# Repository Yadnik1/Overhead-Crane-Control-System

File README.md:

# Overhead-Crane-Control-System
An efficient and reliable embedded system firmware for overhead crane applications. Developed using STM32G030C8T6 MCU, this project presents a specialized solution for encoder and decoder units, tailored to enhance the performance and safety of crane operations. The project firmware comprises three fundamental components: the encoder unit (remote control), the decoder unit (crane control system), and the EEPROM configuration software.

## Decoder Unit

This code serves as the core control unit for an overhead crane system, managing bidirectional communication between master and slave devices using the NRF905 module. It detects the device's operational mode based on the state of the `MODE_Pin` and initializes the NRF905 module, shift registers, and relays during startup. The NRF905 module constantly listens for incoming data, with a rising edge on the `DR_Pin` indicating data reception. Upon receiving specific patterns like `0x40000000`, it activates the NRF905 module and the system eventually, while `0x80000000` sets the receiver state to standby and turns off the system. Relay states are updated through shift registers to control crane operations.

Additionally, the code utilizes timer interrupts to enhance control. The `HAL_TIM_Base_Start_IT(&htim3)` function initiates timer 3 and enables its interrupts, allowing for precise timing operations. Timer interrupts can be used for various purposes within the code, such as coordinating time-sensitive tasks or ensuring precise timing for specific crane operations.

The code not only manages data reception and relay control but also implements crucial button toggle and interlock features. Button presses, particularly those involving button 3, are monitored and toggled through the `button3_state` variable. Interlock functionality is achieved by clearing relay bits associated with buttons 5 and 6 if both buttons are pressed simultaneously. These 2 functionalities are often used in overhead cranes for numerous applications apart from normal relay actuation.

The decoder firmware can be found in the Firmware folder in Decoder.c file.

### Standalone Decoder Unit

## Encoder Unit

The encoder unit interfaces with a set of buttons representing different crane functions, such as movement and relay control. The system relies on the NRF905 wireless module for communication between the encoder unit and the crane's decoder unit. The encoder unit continuously monitors the state of these buttons and generates a 32-bit pattern based on the button configuration. This pattern is then transmitted using the NRF905 module to the decoder unit, allowing it to interpret and execute the corresponding crane operations.

The encoder unit also incorporates timer interrupts, which are crucial for efficient button polling and data transmission. Timer interrupts ensure that button states are checked periodically, preventing excessive data transmission while maintaining responsiveness to button presses. Additionally, the code includes logic for switching on and off specific crane functions based on the received data, enabling the operator to control various aspects of the crane's operation remotely. Overall, the encoder unit plays a vital role in facilitating remote crane control, ensuring safety and precision in crane operations, and enhancing the efficiency of overhead crane systems.

The encoder firmware can be found in the Firmware folder in Encoder.c file.

### Standalone Encoder Unit

### Encoder-Decoder Unit Set

### Powered Encoder-Decoder Unit Set

Additionally, I also worked towards the development of the two-sided encoder unit PCB as seen below: 

### PCB of the Encoder Unit

## EEPROM Configuration

The provided code serves as a critical component for configuring the decoder unit, facilitating the mapping of each key on the encoder to its respective relay on the decoder. This functionality is essential in scenarios where customization and flexibility are paramount, such as when an original equipment manufacturer (OEM) needs to provide a system that can adapt to the unique button-to-relay configurations of multiple clients. The code enables the OEM to initialize and manage memory structures that store the configuration data for different keys and sectors within the decoder. It supports both default settings and runtime customization of these configurations through AT commands received via UART.

The code's working involves several key aspects. First, it initializes the memory with default values for each key and sector, ensuring a consistent starting point. Second, it processes AT commands sent over UART to customize the configuration, allowing the OEM or clients to modify the relay assignments for specific keys dynamically. Third, it employs Flash memory to store these configurations persistently, ensuring that the settings are retained even after power cycles. Lastly, it provides feedback to the user or clients through debug messages sent over UART, facilitating troubleshooting and verification of the configurations. This code serves as a robust and adaptable solution for managing button-to-relay mappings in a versatile and client-specific manner, making it highly valuable for the OEM's system customization needs.

The EEPROM configuration firmware can be found in the Firmware folder in EEPROM.c file.

### Testing and Configuring the Decoder Unit

## Final Application:

The final appliation can be as seen from the image below, where the power circuitry and the enclosure is applied on the encoder and decoder units before sending it to the end client.

### Application Ready Overhead-Crane-Control-System

Complete working of the system before can be seen in this video: https://bit.ly/48JevyT

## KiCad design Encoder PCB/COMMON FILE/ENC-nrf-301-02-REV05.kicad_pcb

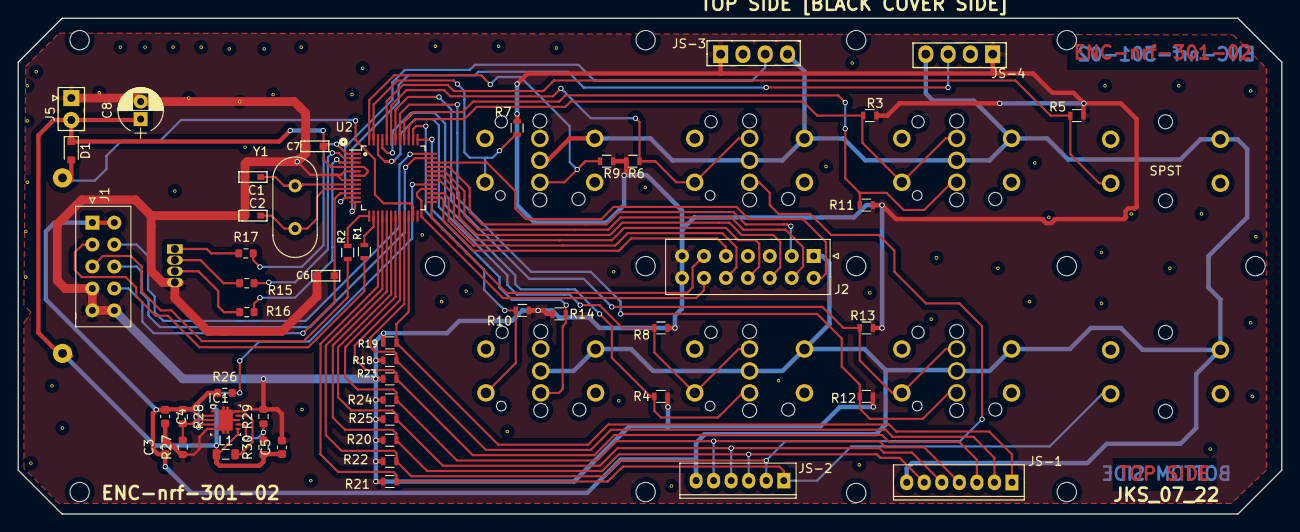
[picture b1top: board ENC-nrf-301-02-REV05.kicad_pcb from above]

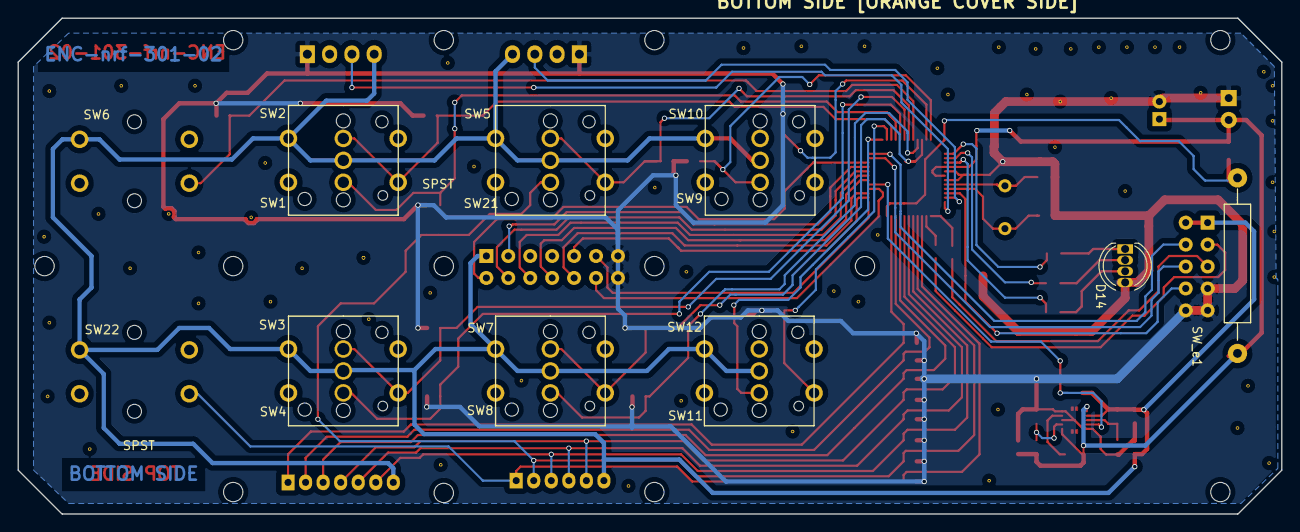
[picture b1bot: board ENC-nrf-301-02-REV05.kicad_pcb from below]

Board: 2 copper layers, 144.0 x 56.5 mm, 66 parts (8 on the bottom side), 54 nets.

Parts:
C1, C2: C; MS_0603
C3: CP1; C_0603_1608Metric
C4, C5: C; C_0603_1608Metric
C6, C7: C; HS_0603
C8: C; CP_Radial_D5.0mm_P2.00mm
D1: D; D_0805
D14: LED_3528; LED_D5.0mm-4
IC1: TPS61020DRCR
J1: CONN_5X2; CON_2X5_2.54MM
J2: CONN_7X2; CONN_2X7_2.54MM
J5: CONN_2; 2.5MM_BERGE
JS-1: CONN_7; CON_2.0MM_7PIN
JS-2: CONN_6; CON_2.0MM_6PIN
JS-3, JS-4: CONN_4; 2.54MM_BERGE_4PIN
L1: L; L_0805_2012Metric
R1, R2, R3, R4, R5, R6, R7, R8, R9, R10, R11, R12, R13, R14, R18, R19, R20, R21, R22, R23, R24, R25: R; R_0603
R15, R16, R17, R26, R27, R28, R29, R30: R; R_0603_1608Metric
SW1, SW4, SW6, SW8, SW9, SW12, SW21, SW22: SPST; SW_ALPS_TACT
SW2, SW3, SW5, SW7, SW10, SW11: SPST; SW_MARKQUARD
SW_e1: RD_RELAY; RELAY_REED_L20W2.5
U2: STM32G030C6T6; LQFP-48_7x7mm_Pitch0.5mm
Y1: Crystal; Crystal_HC49-4H_Vertical

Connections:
+3.3V: C3.1, C4.1, IC1.2, J1.1, J1.2, J2.1, JS-1.7, JS-2.6, JS-3.4, JS-4.4, R26.1, R28.1, SW1.2, SW2.3, SW3.3, SW4.2, SW5.3, SW6.2, SW7.3, SW8.2, SW9.2, SW10.3, SW11.3, SW12.2, SW21.1, SW22.1
/AI1: JS-3.3, U2.11
/AI2: JS-4.3, U2.12
/CD: J2.6, U2.31
/CSN: J2.12, U2.28
/DBG_RX: R1.2, U2.14
/DGB_TX: R2.2, U2.13
/DR: J2.8, U2.30
/MISO: J2.9, U2.26
/MOSI: J2.10, U2.27
/NRST: C6.1, J1.8, U2.10
/PW_UP: J2.4, U2.32
/REED_PIN: D1.2, SW_e1.2, U2.23
/SCK: J2.11, U2.25
/SWCLK: J1.4, U2.36
/SWDIO: J1.6, U2.35
/TRX_CE: J2.3, U2.33
/TX_EN: J2.2, U2.34
/VBAT: C5.1, C7.1, C8.1, D1.1, IC1.1, IC1.6, J5.2, L1.1, R30.1, SW_e1.1, U2.4, U2.6
GND: C1.2, C2.2, C3.2, C4.2, C5.2, C6.2, C7.2, C8.2, D14.4, IC1.5, IC1.8, IC1.10, IC1.11, J1.7, J1.9, J1.10, J2.13, J2.14, J5.1, JS-3.1, JS-4.1, R3.1, R4.1, R5.1, R6.1, R7.1, R8.1, R9.1, R10.1, R11.1, R12.1, R13.1, R14.1, R18.1, R19.1, R20.1, R21.1, R22.1, R23.1, R24.1, R25.1, R27.1, R29.2, U2.5, U2.7
unnamed: C1.1, U2.8, Y1.1
unnamed: C2.1, U2.9, Y1.2
unnamed: R9.2, SW10.2, U2.48
unnamed: R8.2, U2.46
unnamed: R7.2, U2.47
unnamed: R4.2, SW7.2, U2.45
unnamed: R10.2, U2.38
unnamed: R5.2, U2.44
unnamed: R14.2, SW11.2, U2.37
unnamed: R6.2, U2.43
unnamed: R13.2, U2.42
unnamed: R12.2, SW3.2, U2.41
unnamed: R11.2, SW2.2, U2.40
unnamed: R3.2, U2.39
unnamed: D14.1, R17.1
unnamed: D14.2, R15.1
unnamed: D14.3, R16.1
unnamed: JS-1.1, R19.2, U2.22
unnamed: JS-1.2, R18.2, U2.21
unnamed: JS-1.3, R23.2, U2.20
unnamed: JS-1.4, JS-2.5, R24.2, U2.19
unnamed: JS-1.5, JS-2.4, R25.2, U2.18
unnamed: JS-1.6, JS-2.3, R20.2, U2.17
unnamed: JS-2.2, R22.2, SW5.2, U2.16
unnamed: JS-2.1, R21.2, SW22.4, U2.15
unnamed: IC1.3, R27.2, R28.2
unnamed: IC1.4, R26.2
unnamed: IC1.7, R29.1, R30.2
unnamed: IC1.9, L1.2
unnamed: J1.3, R1.1
unnamed: J1.5, R2.1
unnamed: R15.2, U2.2
unnamed: R16.2, U2.3
unnamed: R17.2, U2.1

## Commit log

2024-01-07 Create images
2024-01-07 Create image
